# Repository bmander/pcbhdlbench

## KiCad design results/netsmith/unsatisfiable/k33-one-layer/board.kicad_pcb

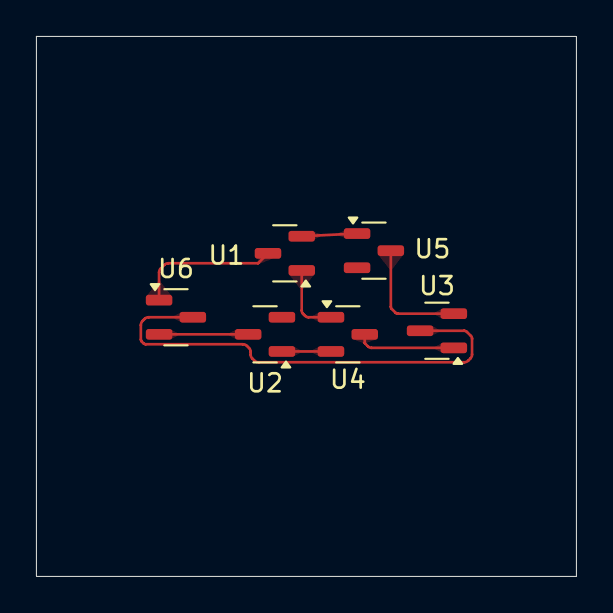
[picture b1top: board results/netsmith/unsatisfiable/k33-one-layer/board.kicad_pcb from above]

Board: 2 copper layers, 30.0 x 30.0 mm, 6 parts (0 on the bottom side), 9 nets.

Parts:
U1, U2, U3, U4, U5, U6: Sot23; SOT-23

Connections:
net-h1.p1: U1.1, U4.1
net-h1.p2: U1.2, U5.1
net-h1.p3: U1.3, U6.1
net-h2.p1: U2.1, U4.2
net-h2.p2: U2.2, U5.2
net-h2.p3: U2.3, U6.2
net-h3.p1: U3.1, U4.3
net-h3.p2: U3.2, U5.3
net-h3.p3: U3.3, U6.3

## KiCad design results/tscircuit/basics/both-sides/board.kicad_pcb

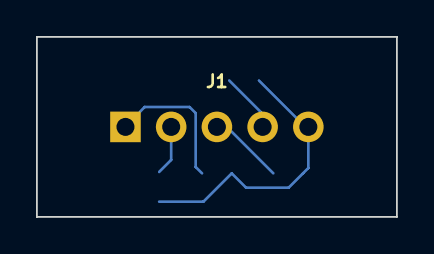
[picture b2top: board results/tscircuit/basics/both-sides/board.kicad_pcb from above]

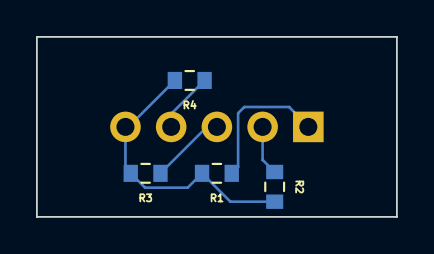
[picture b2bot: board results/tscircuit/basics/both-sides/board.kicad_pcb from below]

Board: 2 copper layers, 20.0 x 10.0 mm, 5 parts (4 on the bottom side), 5 nets.

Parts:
J1: J1; pin_header_pinrow5_p2_54_id1_od1_7_nopinlabels
R1, R2, R3, R4: 10kΩ; resistor_res0603

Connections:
S1: J1.1, R1.1
S2: J1.2, R2.1
S3: J1.3, R3.1
S4: J1.4, R4.1
VCC: J1.5, R1.2, R2.2, R3.2, R4.2

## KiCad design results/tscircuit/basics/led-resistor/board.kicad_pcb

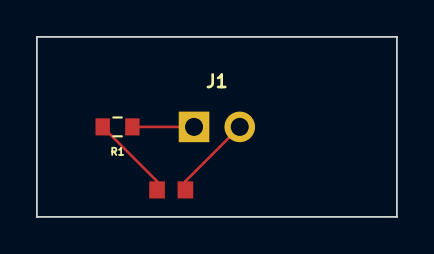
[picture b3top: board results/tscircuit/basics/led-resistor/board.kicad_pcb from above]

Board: 2 copper layers, 20.0 x 10.0 mm, 3 parts (0 on the bottom side), 3 nets.

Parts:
D1: LED; led
J1: J1; pin_header_pinrow2_p2_54_id1_od1_7_nopinlabels
R1: 330Ω; resistor_res0603

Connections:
.D1 > .cathode to .J1 > .pin2: D1.2, J1.2
.J1 > .pin1 to .R1 > .pin1: J1.1, R1.1
.R1 > .pin2 to .D1 > .anode: D1.1, R1.2

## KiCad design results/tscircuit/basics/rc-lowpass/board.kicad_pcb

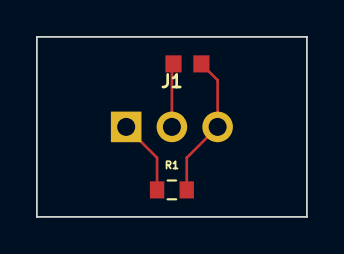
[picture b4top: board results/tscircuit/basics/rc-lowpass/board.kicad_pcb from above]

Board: 2 copper layers, 15.0 x 10.0 mm, 3 parts (0 on the bottom side), 3 nets.

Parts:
C1: 100nF; capacitor
J1: J1; pin_header_pinrow3_p2_54_id1_od1_7_nopinlabels
R1: 10kΩ; resistor_res0603

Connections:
GND: C1.2, J1.2
IN: J1.1, R1.1
OUT: C1.1, J1.3, R1.2

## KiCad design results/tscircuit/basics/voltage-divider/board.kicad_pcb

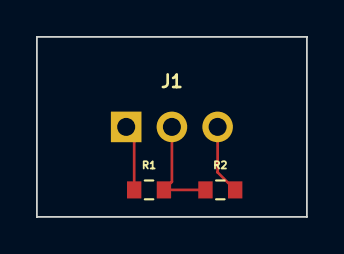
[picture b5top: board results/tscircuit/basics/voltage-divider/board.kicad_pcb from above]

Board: 2 copper layers, 15.0 x 10.0 mm, 3 parts (0 on the bottom side), 3 nets.

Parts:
J1: J1; pin_header_pinrow3_p2_54_id1_od1_7_nopinlabels
R1, R2: 10kΩ; resistor_res0603

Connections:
GND: J1.3, R2.2
VIN: J1.1, R1.1
VOUT: J1.2, R1.2, R2.1

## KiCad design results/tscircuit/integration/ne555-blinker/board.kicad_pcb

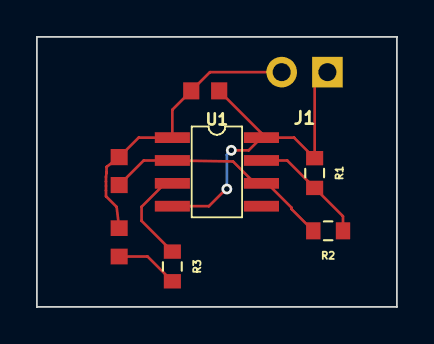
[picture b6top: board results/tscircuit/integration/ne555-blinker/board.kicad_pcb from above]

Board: 2 copper layers, 20.0 x 15.0 mm, 8 parts (0 on the bottom side), 6 nets.

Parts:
C1: 1uF; capacitor
C2: 100nF; capacitor
D1: LED; led
J1: J1; pin_header_pinrow2_p2_54_id1_od1_7_nopinlabels
R1: 1kΩ; resistor_res0603
R2: 470kΩ; resistor_res0603
R3: 330Ω; resistor_res0603
U1: chip_soic8_w6_9mm_pl1_95mm_pw0_6mm

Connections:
DISCH: R1.2, R2.1, U1.7
GND: C1.2, C2.2, D1.2, J1.2, U1.1
LED_A: D1.1, R3.2
OUT: R3.1, U1.3
TRIG: C1.1, R2.2, U1.2, U1.6
VCC: C2.1, J1.1, R1.1, U1.4, U1.8
